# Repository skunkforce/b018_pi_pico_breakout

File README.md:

# edgy_board number b018
This design is part of the [edgy board project](https://github.com/skunkforce/edgy_boards). It provides a breakout of the RP2040 microcontroller. It is used in a few notable compositions: [c001 with ethernet](https://github.com/skunkforce/c001_pi_pico_breakout_with_eth_W5500), [c003 minimal with USB](https://github.com/skunkforce/c003_usb-c_to_minimal_rp2040)

# getting started
This repository uses submodules. After cloning use the command 

```$ git submodule update --init --recursive```

to pull the submodules before opening the project with kicad. 

# Tests
Tests can be found in [TESTS.md](TESTS.md)

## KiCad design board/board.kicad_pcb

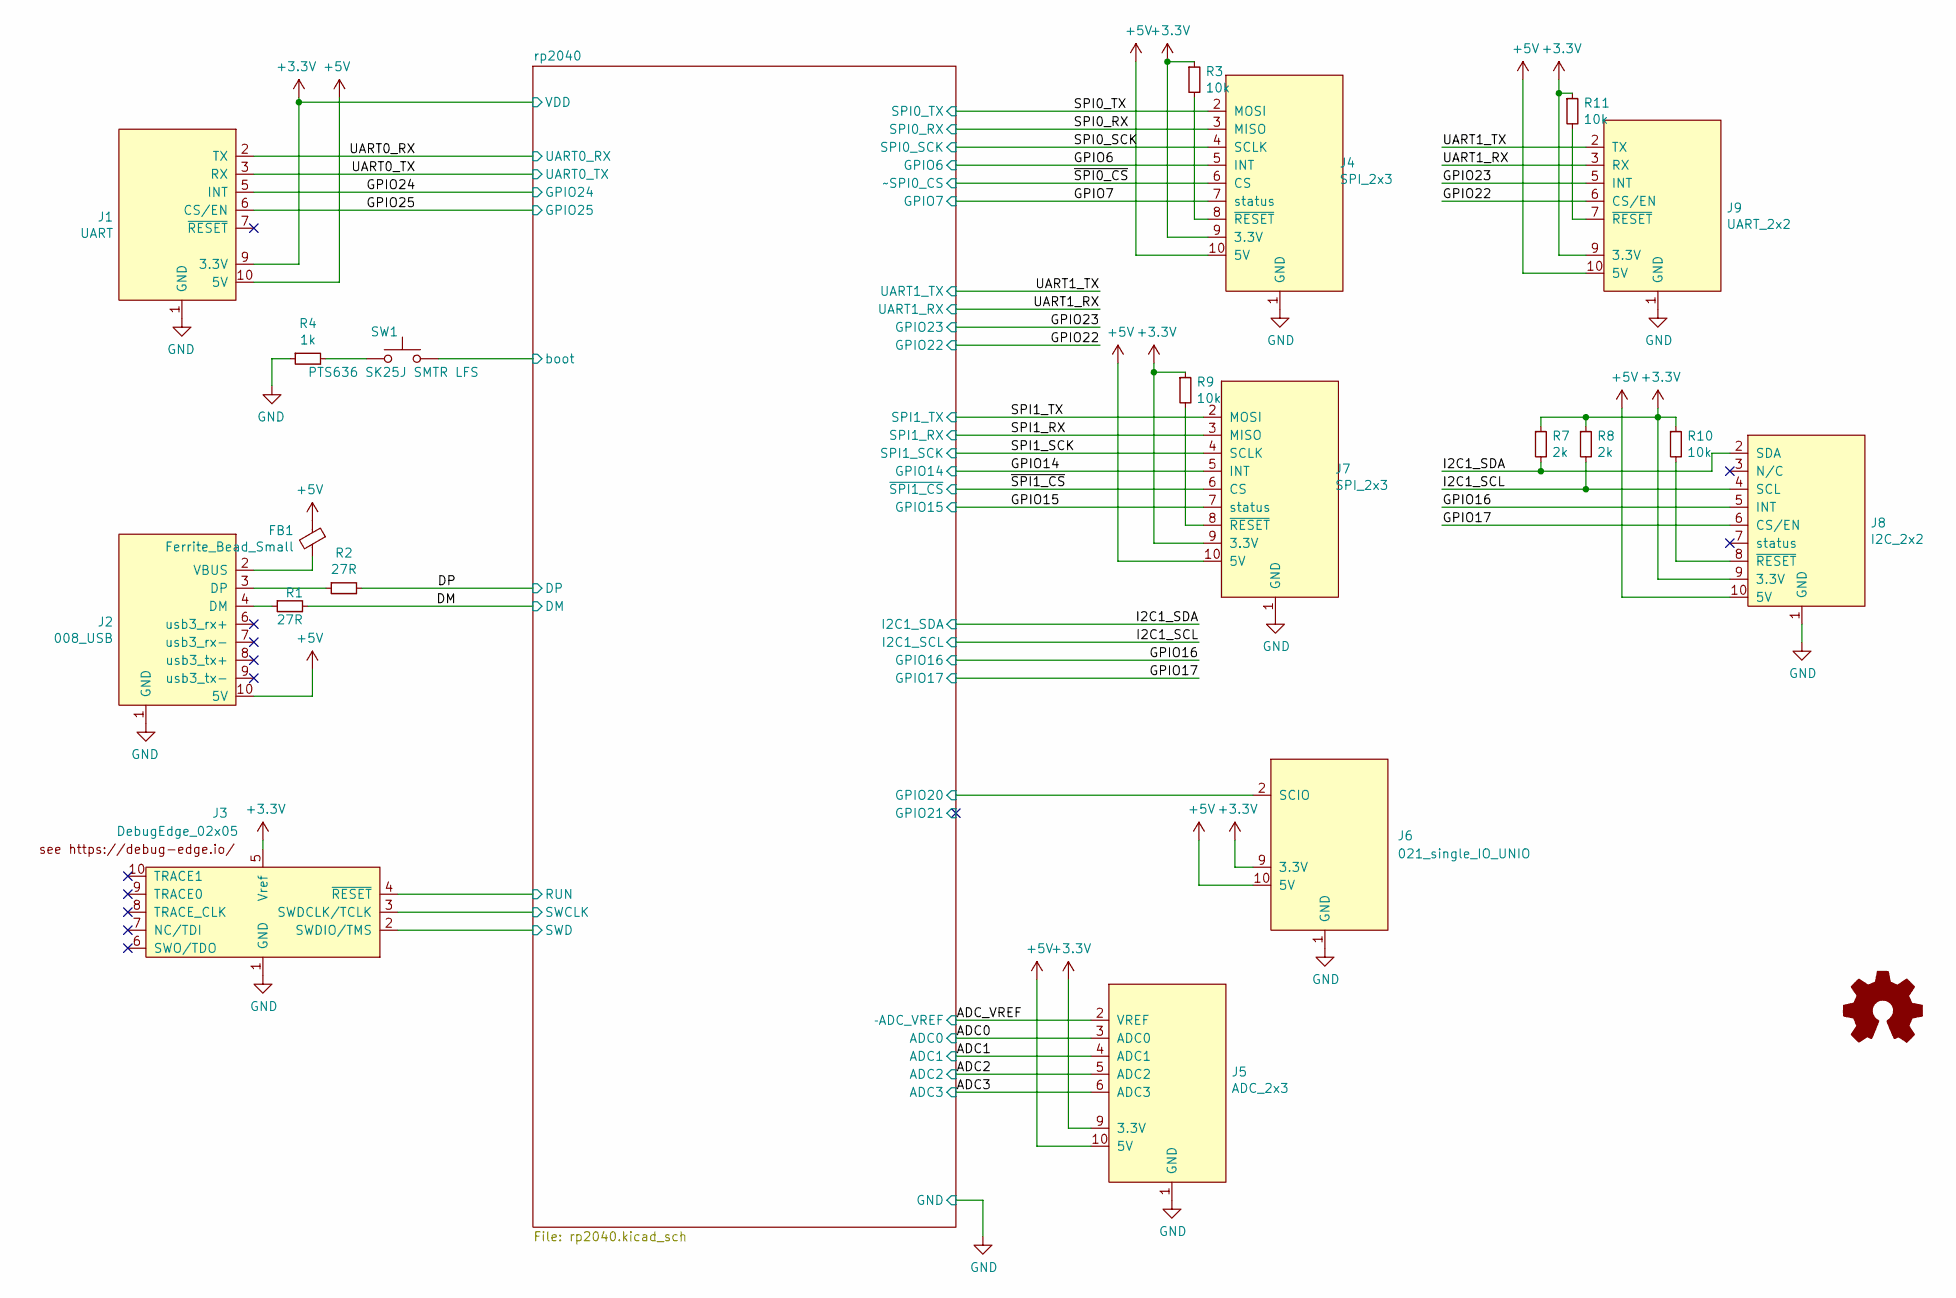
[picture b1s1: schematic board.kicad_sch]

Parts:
FB1: Ferrite_Bead_Small; L_0805_2012Metric; lcsc C17477
J1: UART; on_edge_2x05_device
J2: 008_USB; on_edge_2x05_device
J3: DebugEdge_02x05; debug_edge_2x05_device
J4: SPI_2x3; on_edge_2x05_up_host
J5: ADC_2x3; on_edge_2x05_host
J6: 021_single_IO_UNIO; on_edge_2x05_up_host
J7: SPI_2x3; on_edge_2x05_host
J8: I2C_2x2; on_edge_2x05_host
J9: UART_2x2; on_edge_2x05_host
LOGO1: Logo_Open_Hardware_Small; OSHW-Symbol_6.7x6mm_SilkScreen
R1, R2: 27R; R_0603_1608Metric; lcsc C23140
R3, R9, R10, R11: 10k; R_0603_1608Metric; lcsc C25804
R4: 1k; R_0603_1608Metric; lcsc C21190
R7, R8: 2k; R_0603_1608Metric; lcsc C22975
SW1: PTS636 SK25J SMTR LFS; R_2512_6332Metric; MPN PTS636 SK25J SMTR LFS

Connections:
+3.3V: J1.9 (3.3V), J3.5 (Vref), J4.9 (3.3V), J5.9 (3.3V), J6.9 (3.3V), J7.9 (3.3V), J8.9 (3.3V), J9.9 (3.3V), R3.1, R7.1, R8.1, R9.1, R10.1, R11.1; also elsewhere on the board
+5V: FB1.1, J1.10 (5V), J2.10 (5V), J4.10 (5V), J5.10 (5V), J6.10 (5V), J7.10 (5V), J8.10 (5V), J9.10 (5V)
/ADC0: J5.3 (ADC0); also elsewhere on the board
/ADC1: J5.4 (ADC1); also elsewhere on the board
/ADC2: J5.5 (ADC2); also elsewhere on the board
/ADC3: J5.6 (ADC3); also elsewhere on the board
/ADC_VREF: J5.2 (VREF); also elsewhere on the board
/DM: R1.2; also elsewhere on the board
/DP: R2.2; also elsewhere on the board
/GPIO6: J4.5 (INT); also elsewhere on the board
/GPIO7: J4.7 (status); also elsewhere on the board
/GPIO14: J7.5 (INT); also elsewhere on the board
/GPIO15: J7.7 (status); also elsewhere on the board
/GPIO16: J8.5 (INT); also elsewhere on the board
/GPIO17: J8.6 (CS/EN); also elsewhere on the board
/GPIO22: J9.6 (CS/EN); also elsewhere on the board
/GPIO23: J9.5 (INT); also elsewhere on the board
/GPIO24: J1.5 (INT); also elsewhere on the board
/GPIO25: J1.6 (CS/EN); also elsewhere on the board
/I2C1_SCL: J8.4 (SCL), R8.2; also elsewhere on the board
/I2C1_SDA: J8.2 (SDA), R7.2; also elsewhere on the board
/SPI0_RX: J4.3 (MISO); also elsewhere on the board
/SPI0_SCK: J4.4 (SCLK); also elsewhere on the board
/SPI0_TX: J4.2 (MOSI); also elsewhere on the board
/SPI1_RX: J7.3 (MISO); also elsewhere on the board
/SPI1_SCK: J7.4 (SCLK); also elsewhere on the board
/SPI1_TX: J7.2 (MOSI); also elsewhere on the board
/UART0_RX: J1.2 (TX); also elsewhere on the board
/UART0_TX: J1.3 (RX); also elsewhere on the board
/UART1_RX: J9.3 (RX); also elsewhere on the board
/UART1_TX: J9.2 (TX); also elsewhere on the board
/rp2040/GPIO20: J6.2 (SCIO); also elsewhere on the board
/rp2040/QPI_SS: SW1.2; also elsewhere on the board
/rp2040/RUN: J3.4 (~RESET); also elsewhere on the board
/rp2040/SWCLK: J3.3 (SWDCLK/TCLK); also elsewhere on the board
/rp2040/SWD: J3.2 (SWDIO/TMS); also elsewhere on the board
/~SPI0_CS: J4.6 (CS); also elsewhere on the board
/~SPI1_CS: J7.6 (CS); also elsewhere on the board
GND: J1.1 (GND), J2.1 (GND), J3.1 (GND), J4.1 (GND), J5.1 (GND), J6.1 (GND), J7.1 (GND), J8.1 (GND), J9.1 (GND), R4.1; also elsewhere on the board
unnamed: J2.4 (DM), R1.1
unnamed: J2.3 (DP), R2.1
unnamed: FB1.2, J2.2 (VBUS)
unnamed: J4.8 (~RESET), R3.2
unnamed: J7.8 (~RESET), R9.2
unnamed: J8.8 (~RESET), R10.2
unnamed: J9.7 (~RESET), R11.2
unnamed: R4.2, SW1.1

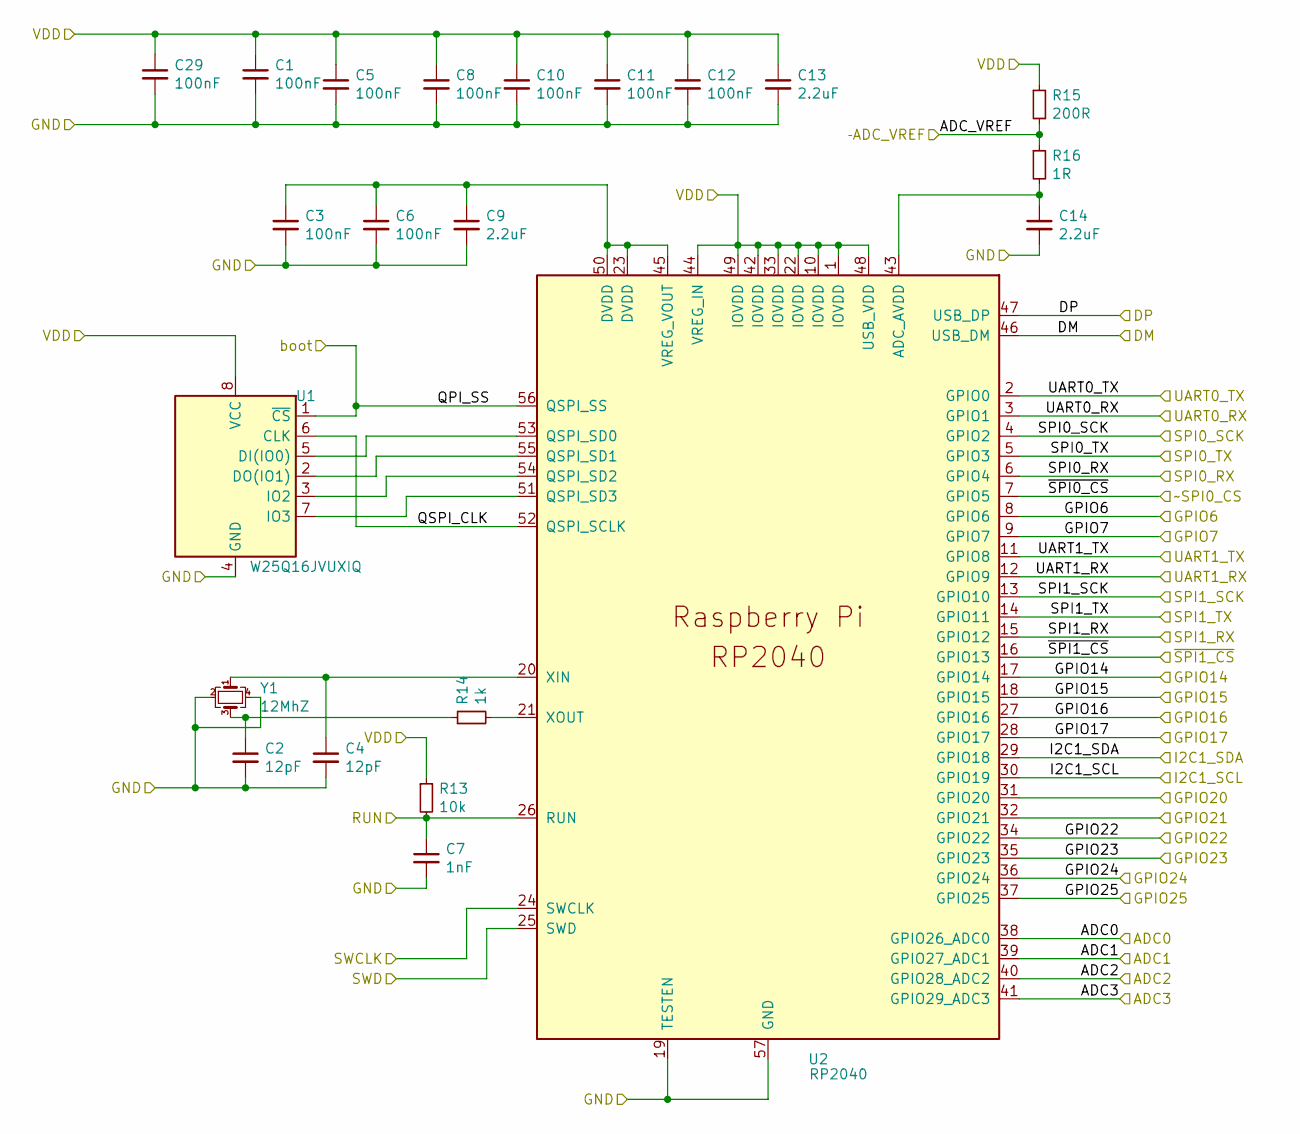
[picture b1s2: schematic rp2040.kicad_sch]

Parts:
C1, C3, C5, C6, C8, C10, C11, C12, C29: 100nF; C_0603_1608Metric; lcsc C14663
C2, C4: 12pF; C_0603_1608Metric; lcsc C38523
C7: 1nF; C_0603_1608Metric; lcsc C1588
C9, C13, C14: 2.2uF; C_0603_1608Metric; lcsc C23630
R13: 10k; R_0603_1608Metric; lcsc C25804
R14: 1k; R_0603_1608Metric; lcsc C21190
R15: 200R; R_0603_1608Metric; lcsc C8218
R16: 1R; R_0603_1608Metric; lcsc C22936
U1: W25Q16JVUXIQ; DFN-8-1EP_3x2mm_P0.5mm_EP1.3x1.5mm; lcsc C2843335
U2: RP2040; QFN-56-1EP_7x7mm_P0.4mm_EP3.2x3.2mm; lcsc C2040
Y1: 12MhZ; Crystal_SMD_Abracon_ABM8G-4Pin_3.2x2.5mm; MPN ABM8G-12.000MHZ-4Y-T3; lcsc C9002

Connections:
+3.3V: C1.1, C5.1, C8.1, C10.1, C11.1, C12.1, C13.1, C29.1, R13.1, R15.1, U1.8 (VCC), U2.1 (IOVDD), U2.10 (IOVDD), U2.22 (IOVDD), U2.33 (IOVDD), U2.42 (IOVDD), U2.44 (VREG_IN), U2.48 (USB_VDD), U2.49 (IOVDD); also elsewhere on the board
/ADC0: U2.38 (GPIO26_ADC0); also elsewhere on the board
/ADC1: U2.39 (GPIO27_ADC1); also elsewhere on the board
/ADC2: U2.40 (GPIO28_ADC2); also elsewhere on the board
/ADC3: U2.41 (GPIO29_ADC3); also elsewhere on the board
/ADC_VREF: R15.2, R16.1; also elsewhere on the board
/DM: U2.46 (USB_DM); also elsewhere on the board
/DP: U2.47 (USB_DP); also elsewhere on the board
/GPIO6: U2.8 (GPIO6); also elsewhere on the board
/GPIO7: U2.9 (GPIO7); also elsewhere on the board
/GPIO14: U2.17 (GPIO14); also elsewhere on the board
/GPIO15: U2.18 (GPIO15); also elsewhere on the board
/GPIO16: U2.27 (GPIO16); also elsewhere on the board
/GPIO17: U2.28 (GPIO17); also elsewhere on the board
/GPIO22: U2.34 (GPIO22); also elsewhere on the board
/GPIO23: U2.35 (GPIO23); also elsewhere on the board
/GPIO24: U2.36 (GPIO24); also elsewhere on the board
/GPIO25: U2.37 (GPIO25); also elsewhere on the board
/I2C1_SCL: U2.30 (GPIO19); also elsewhere on the board
/I2C1_SDA: U2.29 (GPIO18); also elsewhere on the board
/SPI0_RX: U2.6 (GPIO4); also elsewhere on the board
/SPI0_SCK: U2.4 (GPIO2); also elsewhere on the board
/SPI0_TX: U2.5 (GPIO3); also elsewhere on the board
/SPI1_RX: U2.15 (GPIO12); also elsewhere on the board
/SPI1_SCK: U2.13 (GPIO10); also elsewhere on the board
/SPI1_TX: U2.14 (GPIO11); also elsewhere on the board
/UART0_RX: U2.3 (GPIO1); also elsewhere on the board
/UART0_TX: U2.2 (GPIO0); also elsewhere on the board
/UART1_RX: U2.12 (GPIO9); also elsewhere on the board
/UART1_TX: U2.11 (GPIO8); also elsewhere on the board
/rp2040/GPIO20: U2.31 (GPIO20); also elsewhere on the board
/rp2040/GPIO21: U2.32 (GPIO21)
/rp2040/QPI_SS: U1.1 (~CS), U2.56 (QSPI_SS); also elsewhere on the board
/rp2040/QSPI_CLK: U1.6 (CLK), U2.52 (QSPI_SCLK)
/rp2040/RUN: C7.1, R13.2, U2.26 (RUN); also elsewhere on the board
/rp2040/SWCLK: U2.24 (SWCLK); also elsewhere on the board
/rp2040/SWD: U2.25 (SWD); also elsewhere on the board
/~SPI0_CS: U2.7 (GPIO5); also elsewhere on the board
/~SPI1_CS: U2.16 (GPIO13); also elsewhere on the board
GND: C1.2, C2.2, C3.2, C4.2, C5.2, C6.2, C7.2, C8.2, C9.2, C10.2, C11.2, C12.2, C13.2, C14.2, C29.2, U1.4 (GND), U2.19 (TESTEN), U2.57 (GND), Y1.2, Y1.4; also elsewhere on the board
unnamed: C2.1, R14.1, Y1.3
unnamed: U1.5 (DI(IO0)), U2.53 (QSPI_SD0)
unnamed: U1.2 (DO(IO1)), U2.55 (QSPI_SD1)
unnamed: U1.3 (IO2), U2.54 (QSPI_SD2)
unnamed: U1.7 (IO3), U2.51 (QSPI_SD3)
unnamed: C14.1, R16.2, U2.43 (ADC_AVDD)
unnamed: C3.1, C6.1, C9.1, U2.23 (DVDD), U2.45 (VREG_VOUT), U2.50 (DVDD)
unnamed: C4.1, U2.20 (XIN), Y1.1
unnamed: R14.2, U2.21 (XOUT)

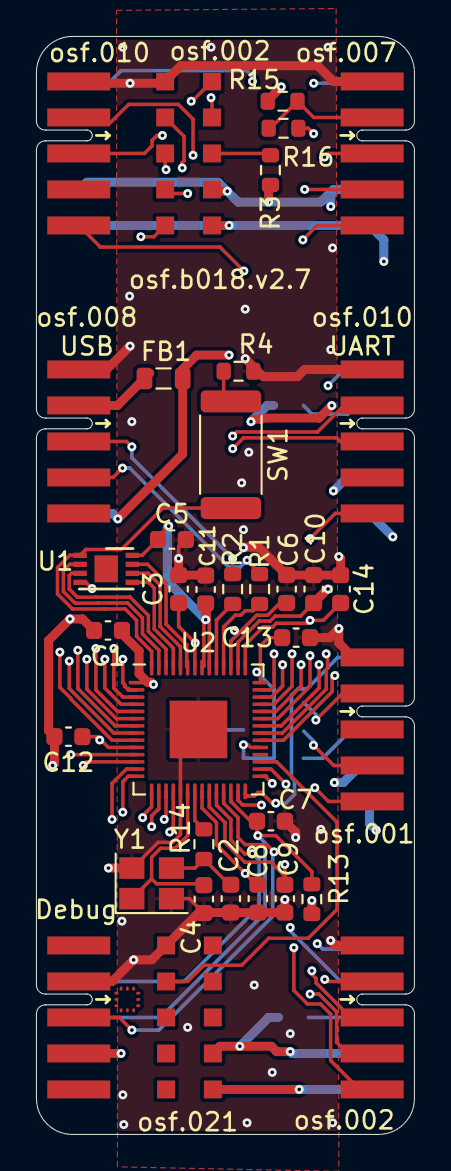
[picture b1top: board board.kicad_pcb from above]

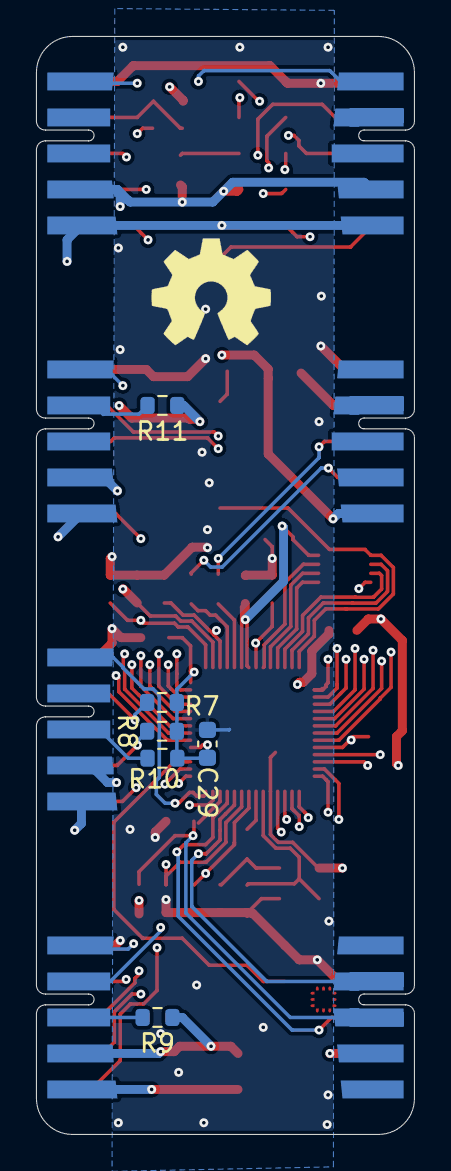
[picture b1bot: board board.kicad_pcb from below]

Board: 4 copper layers, 21.0 x 61.0 mm, 43 parts (7 on the bottom side), 57 nets.

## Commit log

2023-02-16 modernized the legacy version
2023-02-27 changed top I2C connector to be a UNIO connector for a mac address chip
2023-03-01 changed power symbols in subsheets
2023-04-08 updated connector footprints and added planes
2023-11-19 upgraded to new kicad and switched to standard flash
2023-12-29 updated I2C to fixed pinning
2025-07-26 added LCSC part numbers
